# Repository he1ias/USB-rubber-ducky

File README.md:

# USB-rubber-ducky
A USB rubber ducky made for Hack Club's HalfLife event.

### What is a Rubber Ducky?

A Rubber Ducky is a toy hacking tool that can emulate USB keyboards, helping show the limits of what physical access to a device can achieve. 

### Why did you make it?

Because real Rubber Duckies, and other hacking devices like the Flipper Zero, are really expensive! I wanted to show just how powerful even a tiny microcontroller can be, and create something cheap and easy to use with it.

### What can it do?

It can play Snake, run commands on your computer at superhuman speeds, or just make you look like a hacker; among other things.

### How do I use it?

You'll first need to print the PCB and order all the parts (located in `BOM*.csv`, and shown below). Then, simply assemble, plug in the ESP32 and run the code located in `/Firmware`. The microcontroller will spin up its own web interface which can be accessed from your local network.

### What parts do I need?

Note all below prices are in AUD. This repository contains two different BOM.csv versions, one with the original AUD prices and one with the converted USD prices (1 AUD ~= 0.70 USD).

| Item | Description | Qty | Unit Price (AUD) | Line Total (AUD) | Link |
|------|-------------|-----|------------------|------------------|------|
| 1 | ESP32-S3-Zero Mini Development Board (4MB Flash, pre-soldered headers) | 1 | $10.60 | $10.60 | [Link](https://littlebirdelectronics.com.au/products/esp32-s3-mini-development-board-based-on-esp32-s3fh4r2-dual-core-processor-240mhz-running-frequency-2-4ghz-wi-fi-bluetooth-5?collection=esp32-development-boards&variant=WS-25517) |
| 2 | Female 10-pin header (PTH, 0.1") | 2 | $1.60 | $3.20 | [Link](https://littlebirdelectronics.com.au/products/header-10-pin-female-pth-0-1) |
| 3 | Little Bird Lorikeet WS2812B rainbow board (right angle header) | 1 | $3.50 | $3.50 | [Link](https://littlebirdelectronics.com.au/products/little-bird-lorikeet-ws2812b-rainbow-board-with-right-angle-header) |
| 4 | Tactile button (SMD, 12mm) | 2 | $1.65 | $3.30 | [Link](https://littlebirdelectronics.com.au/products/tactile-button-smd-12mm) |
| 5 | 470 ohm 0.5W metal film resistors (pack of 8) | 1 | $0.70 | $0.70 | [Link](https://littlebirdelectronics.com.au/products/470-ohm-0-5-watt-metal-film-resistors-pack-of-8) |
| 6 | OTG converter USB 3.0 to USB-C adapter | 1 | $2.40 | $2.40 | [Link](https://littlebirdelectronics.com.au/products/otg-converter-usb-3-0-convert-to-usb-c) |
| | **Total** | | | **$23.70** | |

### How was it made?

Using KiCad!

I first drew the schematic - this was pretty straightforward, all I had to do was connect up a few buttons, resistors, and a display to the ESP32:

...and then routed my PCB! I put a decent amount of effort into making sure the Ducky would be easy to use, and I think my finalised PCB found the right balance between simplicity and usability. The 5 LED display, for instance, can triple as a payload selector, progress indicator, and status light!

Given this was my first PCB, I am happy with how it turned out! My full Half Life journal log can be found in `JOURNAL.md`.

Thanks for reading :)

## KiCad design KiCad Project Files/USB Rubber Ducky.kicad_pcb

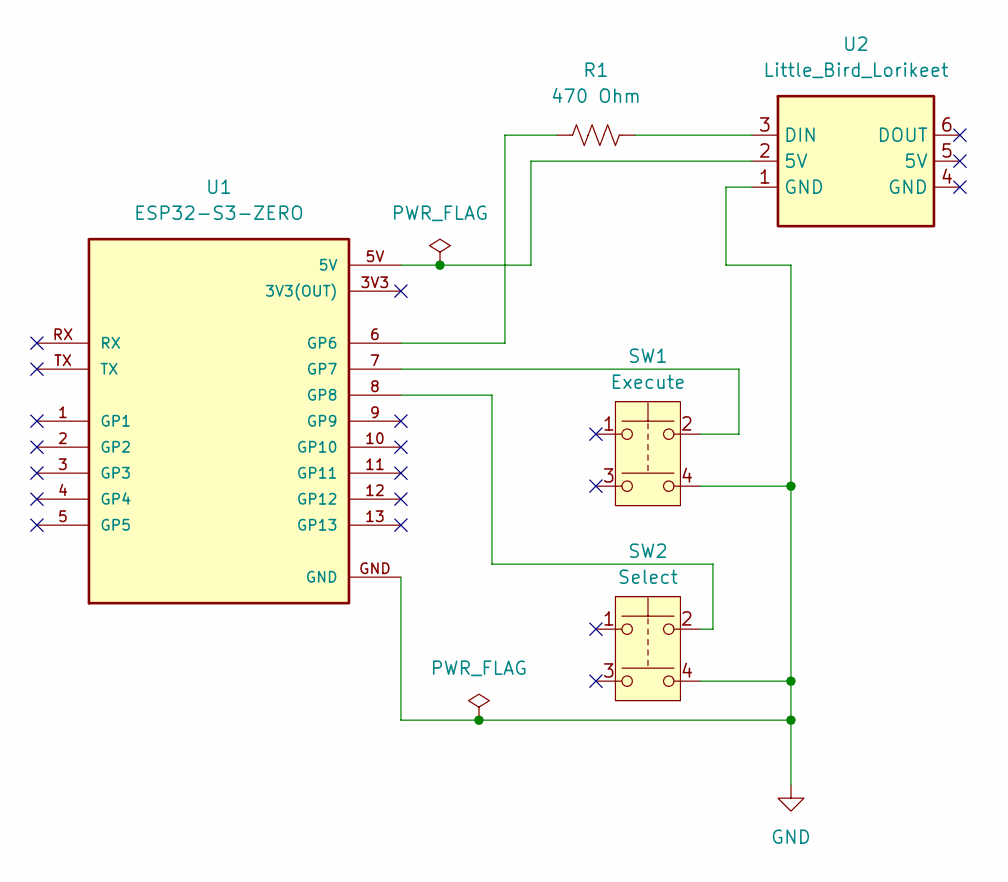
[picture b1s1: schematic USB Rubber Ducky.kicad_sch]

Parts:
R1: 470 Ohm; R_Axial_DIN0207_L6.3mm_D2.5mm_P10.16mm_Horizontal
SW1: Execute; SW_Push_12x12mm_TL3300
SW2: Select; SW_Push_12x12mm_TL3300
U1: ESP32-S3-ZERO; MODULE_ESP32-S3-ZERO_10PIN; PARTREV NA
U2: Little_Bird_Lorikeet

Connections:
GND: SW1.4, SW2.4, U1.GND, U2.1 (GND)
unnamed: R1.1, U1.6 (GP6)
unnamed: SW1.2, U1.7 (GP7)
unnamed: SW2.2, U1.8 (GP8)
unnamed: U1.5V, U2.2 (5V)
unnamed: R1.2, U2.3 (DIN)

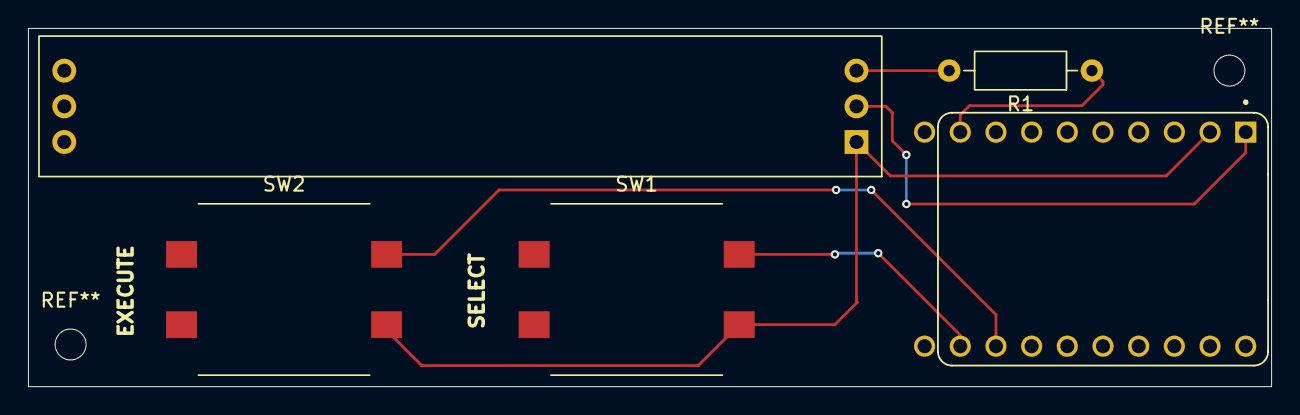
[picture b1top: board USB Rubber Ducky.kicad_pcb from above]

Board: 2 copper layers, 88.5 x 25.5 mm, 5 parts (0 on the bottom side), 6 nets.
